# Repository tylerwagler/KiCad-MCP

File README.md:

# KiCad MCP Server

AI-assisted PCB design through the [Model Context Protocol](https://modelcontextprotocol.io). Analyze, modify, route, verify, and export KiCad boards — all from your AI assistant.

**152 tools** | **918 tests (684 pass, 234 env-gated skips)** | **Pure Python, zero KiCad dependency for reads**

## What It Does

This MCP server gives AI assistants (Claude, etc.) full access to KiCad PCB design workflows:

- **Open and analyze** boards, schematics, and libraries without KiCad installed
- **Place, move, rotate, flip, edit, and replace** components with full undo/rollback
- **Route traces and vias**, manage nets and zones, add copper pours
- **Run DRC** and check manufacturability against JLCPCB/OSHPark/PCBWay rules
- **Export** Gerber, PDF, SVG, STEP, VRML, BOM, and pick-and-place files
- **Create projects** and schematics from scratch

## Quick Start

### Install

```bash
# Requires Python 3.11+
uv sync --all-extras
```

### Configure Your AI Client

Add to your MCP client configuration (e.g. Claude Desktop `claude_desktop_config.json`):

```json
{
  "mcpServers": {
    "kicad-mcp": {
      "command": "uv",
      "args": ["--directory", "/path/to/KiCad-MCP", "run", "kicad-mcp"]
    }
  }
}
```

### Run Standalone

```bash
uv run kicad-mcp
```

## Tool Categories

| Category | Tools | Description |
|---|---|---|
| **Project** | 6 | Open/create/save projects, list components, board info |
| **Board Setup** | 7 | Board size, outline, mounting holes, text, design rules |
| **Placement** | 8 | Place, rotate, flip, delete, edit, replace, group components |
| **Routing** | 5 | Route traces, add/delete vias, ratsnest analysis |
| **Net/Zone** | 7 | Create/delete nets, zones, copper pours, net classes |
| **Schematic** | 11 | Open/edit schematics, add symbols/wires/labels, generate netlists |
| **Analysis** | 6 | Net list, layer stack, board extents, clearance checks |
| **DRC** | 2 | Design rule check with violation details |
| **Export** | 7 | Gerber, PDF, SVG, STEP, VRML, BOM, pick-and-place |
| **Library** | 6 | Search symbols/footprints across installed KiCad libraries |
| **Manufacturer** | 3 | DRC presets for JLCPCB, OSHPark, PCBWay |
| **Session** | 7 | Start/commit/rollback sessions, preview moves, undo changes |

## Architecture

### Two-Tier Tool Router

Not all 152 tools are dumped into the LLM context. Instead:

- **9 direct tools** are always visible (open project, start session, etc.)
- **143 routed tools** are discoverable via 4 meta-tools: `list_tool_categories`, `get_category_tools`, `execute_tool`, `search_tools`

This reduces LLM context usage by ~70%.

### Three Backends

1. **S-expression parser** — Pure Python, zero dependencies. Reads `.kicad_pcb`, `.kicad_sch`, `.kicad_mod` files directly. Used for all read operations. KiCad does **not** need to be installed.
2. **kicad-cli** — Wraps KiCad's official CLI (KiCad 8+) for DRC, Gerber export, PDF rendering. Auto-detects install path on Windows/Linux/macOS.
3. **KiCad IPC API** — For real-time UI sync when KiCad is running (KiCad 9+, planned).

### Session Model (Query-Before-Commit)

All board mutations go through a safe transaction model:

```
start_session → query_move (preview) → apply_move → undo → commit / rollback
```

The AI can preview changes before applying, undo individual operations, and rollback entire sessions. Nothing touches disk until `commit_session`.

### Three-Pillar MCP Design

Following the full MCP specification:

- **Tools** — Actions that modify state (152 tools)
- **Resources** — Read-only board data (component list, net map, board summary)
- **Prompts** — Conversation templates (DRC troubleshooting, design review, placement guidance)

## Development

```bash
# Install with dev dependencies
uv sync --all-extras

# Run tests
uv run pytest

# Lint and format
uv run ruff check .
uv run ruff format .

# Type check
uv run mypy src/
```

### Project Structure

```
src/kicad_mcp/
├── server.py              # FastMCP server entry point
├── state.py               # Global board state
├── schematic_state.py     # Global schematic state
├── security.py            # Path validation, subprocess guards
├── tools/
│   ├── registry.py        # ToolSpec + TOOL_REGISTRY (single source of truth)
│   ├── router.py          # 4 meta-tools for dynamic discovery
│   ├── board_setup.py     # Board size, outline, text, design rules
│   ├── placement.py       # Component placement, edit, replace, group
│   ├── routing.py         # Traces, vias, ratsnest
│   ├── netzone.py         # Nets, zones, copper pours, net classes
│   ├── schematic.py       # Schematic editing, netlist generation
│   ├── analysis.py        # Board analysis, clearance checks
│   ├── export.py          # Gerber, PDF, SVG, STEP, VRML, BOM
│   ├── drc.py             # Design rule checking
│   ├── library.py         # KiCad library search
│   ├── manufacturer.py    # Manufacturer DRC presets
│   ├── project.py         # Project create/save
│   ├── mutation.py        # Session start/commit/rollback/undo
│   └── direct.py          # Core direct tools (open project, etc.)
├── session/
│   └── manager.py         # SessionManager with undo/rollback
├── backends/
│   └── kicad_cli.py       # kicad-cli wrapper (DRC, export)
├── sexp/
│   ├── parser.py          # Zero-dependency S-expression parser
│   └── document.py        # Document model with round-trip fidelity
├── schema/                # Typed KiCad models (board, schematic, footprint)
├── resources/             # MCP Resources (read-only board state)
├── prompts/               # MCP Prompt templates
└── manufacturers/         # DRC presets (JLCPCB, OSHPark, PCBWay)
```

## Requirements

- **Python 3.11+**
- **KiCad 8+** (optional — only needed for DRC and export commands; board reading works without it)
- **uv** (recommended) or pip

## License

GPL-3.0 — matching KiCad itself.

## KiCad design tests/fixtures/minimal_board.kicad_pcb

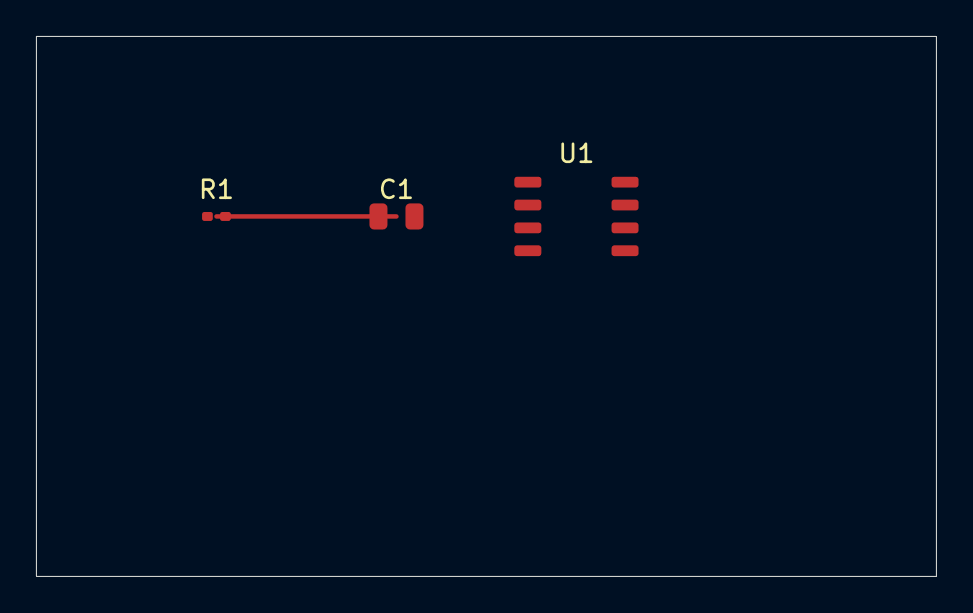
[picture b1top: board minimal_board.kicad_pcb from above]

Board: 2 copper layers, 50.0 x 30.0 mm, 3 parts (0 on the bottom side), 2 nets.

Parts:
C1: 100nF; C_0805_2012Metric
R1: 10k; R_0402_1005Metric
U1: ATtiny85; SOIC-8_3.9x4.9mm_P1.27mm

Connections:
GND: C1.2, R1.2, U1.4
VCC: C1.1, R1.1, U1.1, U1.8

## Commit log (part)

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2026-02-27 Fork commit: Fix IPC API tests and security hardening
    - Fix 7 failing IPC tests (test_create_track_segment, test_create_via, test_create_zone
    and corresponding tool handler tests) by using proper mock classes that bypass
    kipy's protobuf CopyFrom mechanism
    - Add path traversal detection in PathValidator to catch patterns like ../../etc/passwd
    - Add absolute path rejection in SecureSubprocess with suspicious path detection
    - Add 25 new security tests covering path validation and subprocess safety
2026-02-27 Fix security vulnerabilities from audit report
    - Allow absolute paths with export extensions (.pdf, .svg, .gerber, etc.)
    to support legitimate kicad-cli export operations
    - Add 'plain' to format whitelist for DRC report generation
    - Support comma-separated layer values (--layers F.Cu,Edge.Cuts)
    - Update _looks_like_path to recognize export extensions
    Changes based on audit audit-02272026 findings:
2026-02-27 Fix correctness issues from audit report
    - Fix undo logic bug in manager.py:362/374: use parse_all() instead of
    splitting snapshots by newlines (handles multi-line S-expressions)
    - Fix add_board_outline undo: properly remove all Edge.Cuts gr_line nodes
    - Fix _VALID_SETUP_RULES: add as SessionManager class attribute for
    backward compatibility with tests
    - Fix IPC API type mismatch in _nm_to_mm(): check isinstance(nm, float)
2026-02-27 Fix rate limiter race condition
    - Change _rate_limit_buckets from dict[str, float] to dict[str, list[float]]
    - Properly implement sliding window rate limiting per tool
    - Atomic check and add within asyncio lock prevents race conditions
    The previous implementation only stored the last timestamp per tool,
    effectively limiting to 1 request per tool per window instead of 100.
    This fix properly tracks all requests in the window while maintaining
2026-02-27 Fix incomplete undo implementation using UUID-based identification
    - add_mounting_hole undo: Use UUID instead of string comparison to
    reliably identify and remove mounting holes
    - add_board_text undo: Use UUID instead of string comparison to
    reliably identify and remove text elements
    - flip_component undo: Prefer UUID matching via before_snapshot, fall
    back to reference designator for backward compatibility
2026-02-27 Add input validation to schematic tools to prevent S-expression injection
    - Added validation functions:
    - _validate_net_name(): Validates net names
    - _validate_layer_name(): Validates layer names
    - _validate_reference(): Validates reference designators
    - _validate_value(): Validates component values
    - _validate_lib_id(): Validates library symbol IDs
2026-02-27 Fix O(N²) in A* pathfinding by adding closed_set
    - Added closed_set to track visited nodes
    - Skip nodes already processed to prevent O(N²) lookups
    - This converts from O(N²) to O(N log N) complexity
    Before: List lookup used for each neighbor check
    After: Set lookup provides O(1) average-case lookup
    The closed_set prevents re-processing nodes that were already expanded,
2026-02-27 Add error handling for file I/O and parsing operations
    - Document.load(): Added try/except for:
    - FileNotFoundError handling
    - PermissionError for file read access
    - UnicodeDecodeError for invalid encoding
    - OSError for general I/O errors
    - ValueError for parsing errors with enhanced messages
2026-02-27 Optimize deep_copy_doc() using SExp.deep_copy() method
    - Added deep_copy() method to SExp class for O(tree_nodes) copying
    - Replaces previous O(file_size) re-parsing approach
    - Performance: ~0.33ms per copy vs ~10-100ms for re-parsing large files
    The new deep_copy() recursively copies the S-expression tree without
    re-parsing the raw text, providing:
    - O(N) time complexity where N = number of nodes
2026-02-27 Move magic numbers to constants module
    Created src/kicad_mcp/constants.py with:
    - MAX_ITERATIONS_DEFAULT = 500_000 (A* safety limit)
    - MAX_RESPONSE_CHARS = 50_000 (response truncation)
    - DEFAULT_VIA_COST = 5.0 (A* layer change penalty)
    - BOARD_OUTLINE_STROKE_WIDTH = 0.05 (mm)
    Updated files:
2026-02-27 Standardize error handling with custom exceptions
    Created exception hierarchy in exceptions.py:
    - KicadMcpError (base exception with error_code and to_dict())
    - ValidationError, ResourceNotFoundError, RateLimitExceededError
    - BackendError, KiCadCliError, IpcError, SessionError
    - SecurityError, ToolExecutionError, BoardLoadingError
    Updated placement_ops.py:
2026-03-07 feat: production readiness audit and implementation plan
    Comprehensive audit of the KiCad MCP server for production deployment.
    ## What Was Done
    ### Code Quality Improvements
    - Fixed all ruff linting errors (5 unused imports auto-removed)
    - Verified zero mypy type errors across entire codebase
    - All 519 unit tests passing
